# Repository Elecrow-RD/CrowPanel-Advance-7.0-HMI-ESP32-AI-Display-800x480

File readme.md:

## Menu
### 1, Product picture
### 2, Product version number
### 3, product information
### 4, Use the driver module
### 5,Quick Start
### 6,Folder structure.
### 7,Pin definition
### 8,Guidelines for downloading some of the files from the github repository

### 1, Product picture

#### 2, Product version number

|      | Hardware | Software | Remark |
| ---- | -------- | -------- | ------ |
| 1    | V1.0     | V1.0     | old    |
| 2    | V1.2     | V1.2     | latest |

### 3, product information

| Main Chip-ESP32-S3-WROOM-1-N16R8         |                                                              |
| -------------------------------------------- | ------------------------------------------------------------ |
| CPU/SoC                                      | high-performance Xtensa 32-bit LX7 dual-core processor, with up to 240MHz |
| System Memory                                | 512KB SRAM、8M PSRAM                                         |
| Memory                                       | 16M Flash，384KB ROM                                         |
| Development Language                         | MicroPython、C/C++                                           |
| Development Environment                      | ESP-IDF、Arduino IDE、PlatformIO、Micro Python、LVGL         |
| **Screen**                                   |                                                              |
| Size                                         | 7.0 inch                                                     |
| Diver IC                                     | SC7277                                                       |
| Resolution                                   | 800*480                                                      |
| Display Panel                                | IPS Panel                                                    |
| Touch Panel                                  | Capacitive Single Touch                                      |
| Viewing Angle                                | 178°                                                         |
| Brightness                                   | 400 cd/m²(Typ.)                                              |
| Color Depth                                  | 16-bit                                                       |
| **Wireless Communication - Onboard Antenna** |                                                              |
| WiFi                                         | Support 2.4GHz, 802.11a/b/g/n                                |
| Bluetooth                                    | Support Bluetooth 5.0 and BLE                                |
| Other                                        | **Zigbee、LoRa、nRF2401、Matter、Thread and Wi-Fi 6 (Optional)** |
| **Interface/Function**                       |                                                              |
| Interface                                    | USB port, UART, I2C, SD card slot, battery socket, speaker port, microphone, etc. |
| Function                                     | RTC clock, audio amplifier, volume control, battery charge management, USB to UART, etc. |
| **Button/LED Indicator**                     |                                                              |
| Reset Button                                 | Yes, press to reset the device                               |
| Boot Button                                  | Yes, press and hold the power button to burn the program     |
| PWR                                          | Power indicator                                              |
| CHG                                          | Lithium battery charging status, completion indication       |
| **Other**                                    |                                                              |
| Installation method                          | Back hanging, fixed hole                                     |
| Operating temperature                        | -20~70 °C                                                    |
| Storage temperature                          | -30~80 °C                                                    |
| Power Input                                  | 5V/2A, USB or UART terminal                                  |
| Active Area                                  | 156mm*87mm                                                   |
| Dimensions                                   | 181.26*108.36*16mm                                           |

### 4, Use the driver module

| Name | dependency library                      |
| ---- | --------------------------------------- |
| LVGL | lvgl/lvgl@8.3.3                         |
|      | Adafruit GFX Library<br/>version=1.11.0 |

### 5,Quick Start
### Arduino IDE starts

#### Teaching Case Path：./example/example_code7.0

1.Download the library files used by this product to the 'libraries' folder.

C:\Users\Documents\Arduino\libraries\

2.Open the Arduino IDE

3.Open the code configuration environment and burn it

### ESP-IDF starts

#### Teaching Case Path：./example/idf_code

1.Right-click on an empty space in the project folder and select "Open with VS Code" to open the project.

2.In the IDF plug-in, select the port, then compile and flash

### 6,Folder structure.

|--3D file： Contains 3D model files (.stp) for the hardware. These files can be used for visualization, enclosure design, or integration into CAD software.

|--Datasheet: Includes datasheets for components used in the project, providing detailed specifications, electrical characteristics, and pin configurations.

|--Eagle_SCH&PCB: Contains **Eagle CAD** schematic (`.sch`) and PCB layout (`.brd`) files. These are used for circuit design and PCB manufacturing.

|--example: Provides example code and projects to demonstrate how to use the hardware and libraries. These examples help users get started quickly.

|--factory_firmware: Stores pre-compiled factory firmware that can be directly flashed onto the device. This ensures the device runs the default functionality.

|--factory_sourcecode:  Contains the source code for the factory firmware, allowing users to modify and rebuild the firmware as needed.

|--libraries: Includes necessary libraries required for compiling and running the project. These libraries provide drivers and additional functionalities for the hardware.

|--Squareline_studio Instructions for use: Squareline_studio instructions: Demonstrate the use of squareline studio.

### 7,Pin definition

#define HSPI_MISO  4
#define HSPI_MOSI  6
#define HSPI_SCLK  5
#define HSPI_SS    19

#define SD_MOSI 6
#define SD_MISO 4
#define SD_SCK  5
#define SD_CS   7 //The chip selector pin is not connected to IO

#define I2S_DOUT 12
#define I2S_BCLK 13
#define I2S_LRC 11

cfg.pin_sclk = 42;  // SPI、SCLK

cfg.pin_mosi = 39;  // SPI、CLK

cfg.pin_miso = -1;  // SPI、MISO

cfg.pin_dc = 41; 

#define TOUCH_GT911_SCL 16
#define TOUCH_GT911_SDA 15

### 8,Guidelines for downloading some of the files from the github repository

##### 1, open the link in your browser: https://downgit.github.io/

##### 2, paste the URL of the GitHub destination folder in the input box (example format: `https://github.com/username/repository name/tree/branch name/folder path`)

##### 3, even a that way to download the file.

①Click the “Create Download Link” button to create a download link, copy the link and open it with your browser to download the contents of the corresponding folder directly.

②Click Download, and you can also download it directly.

#### Note: DownGit downloads are stored by default in **your browser's default downloads folder**, usually:

- **Windows**: `C:\Users\your username\Downloads\` (downloads folder)
- **macOS**: `~/Downloads/` (downloads folder)
- **Linux**: `~/Downloads/` (Downloads folder)

If you change the default download path in your browser, the file will be stored in the download location you set. You can find the downloaded file path in your browser's **Download History** (shortcut `Ctrl + J` or `Cmd + J`).

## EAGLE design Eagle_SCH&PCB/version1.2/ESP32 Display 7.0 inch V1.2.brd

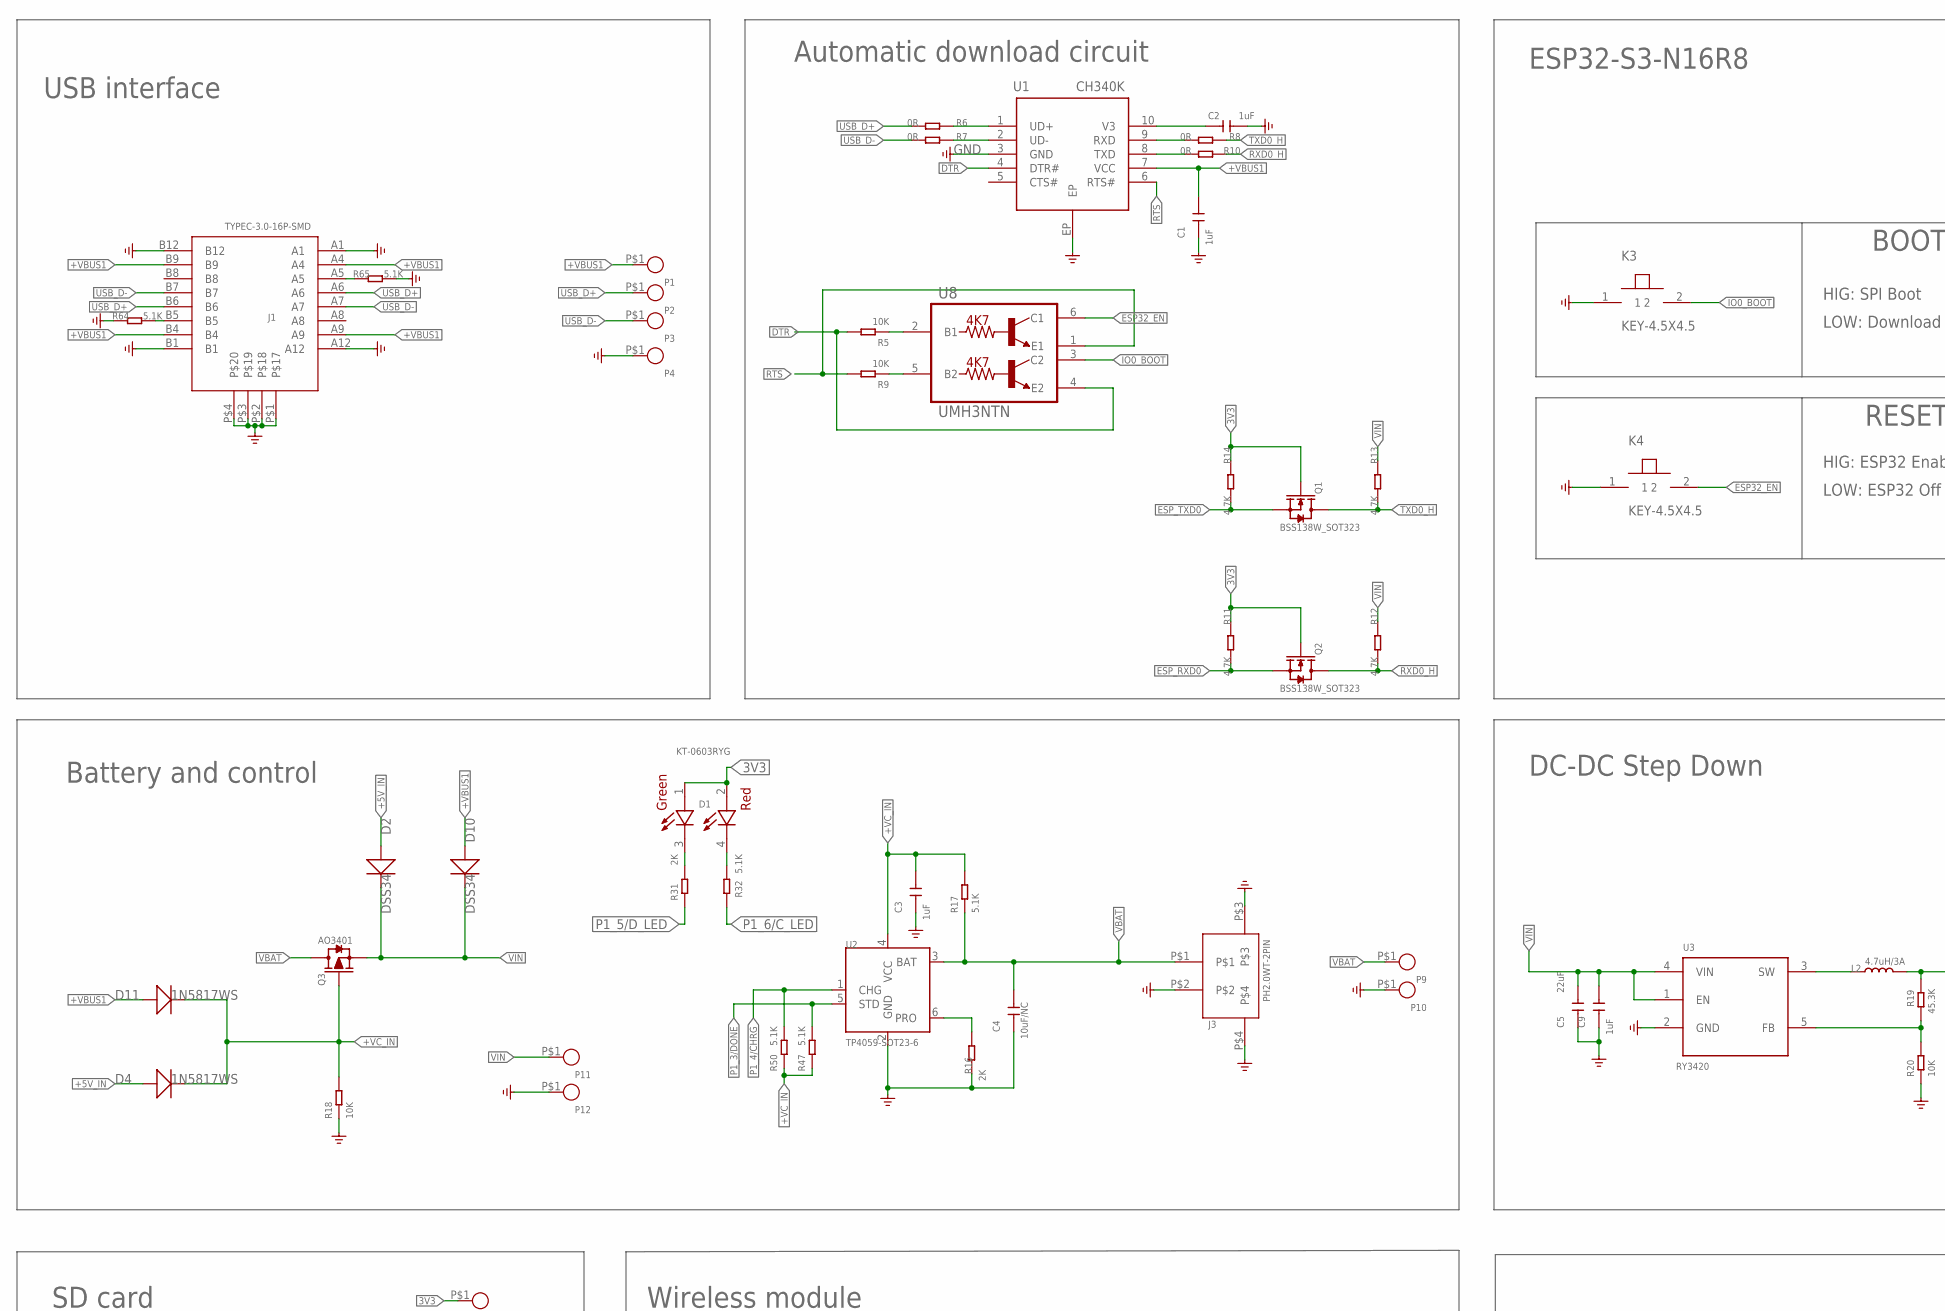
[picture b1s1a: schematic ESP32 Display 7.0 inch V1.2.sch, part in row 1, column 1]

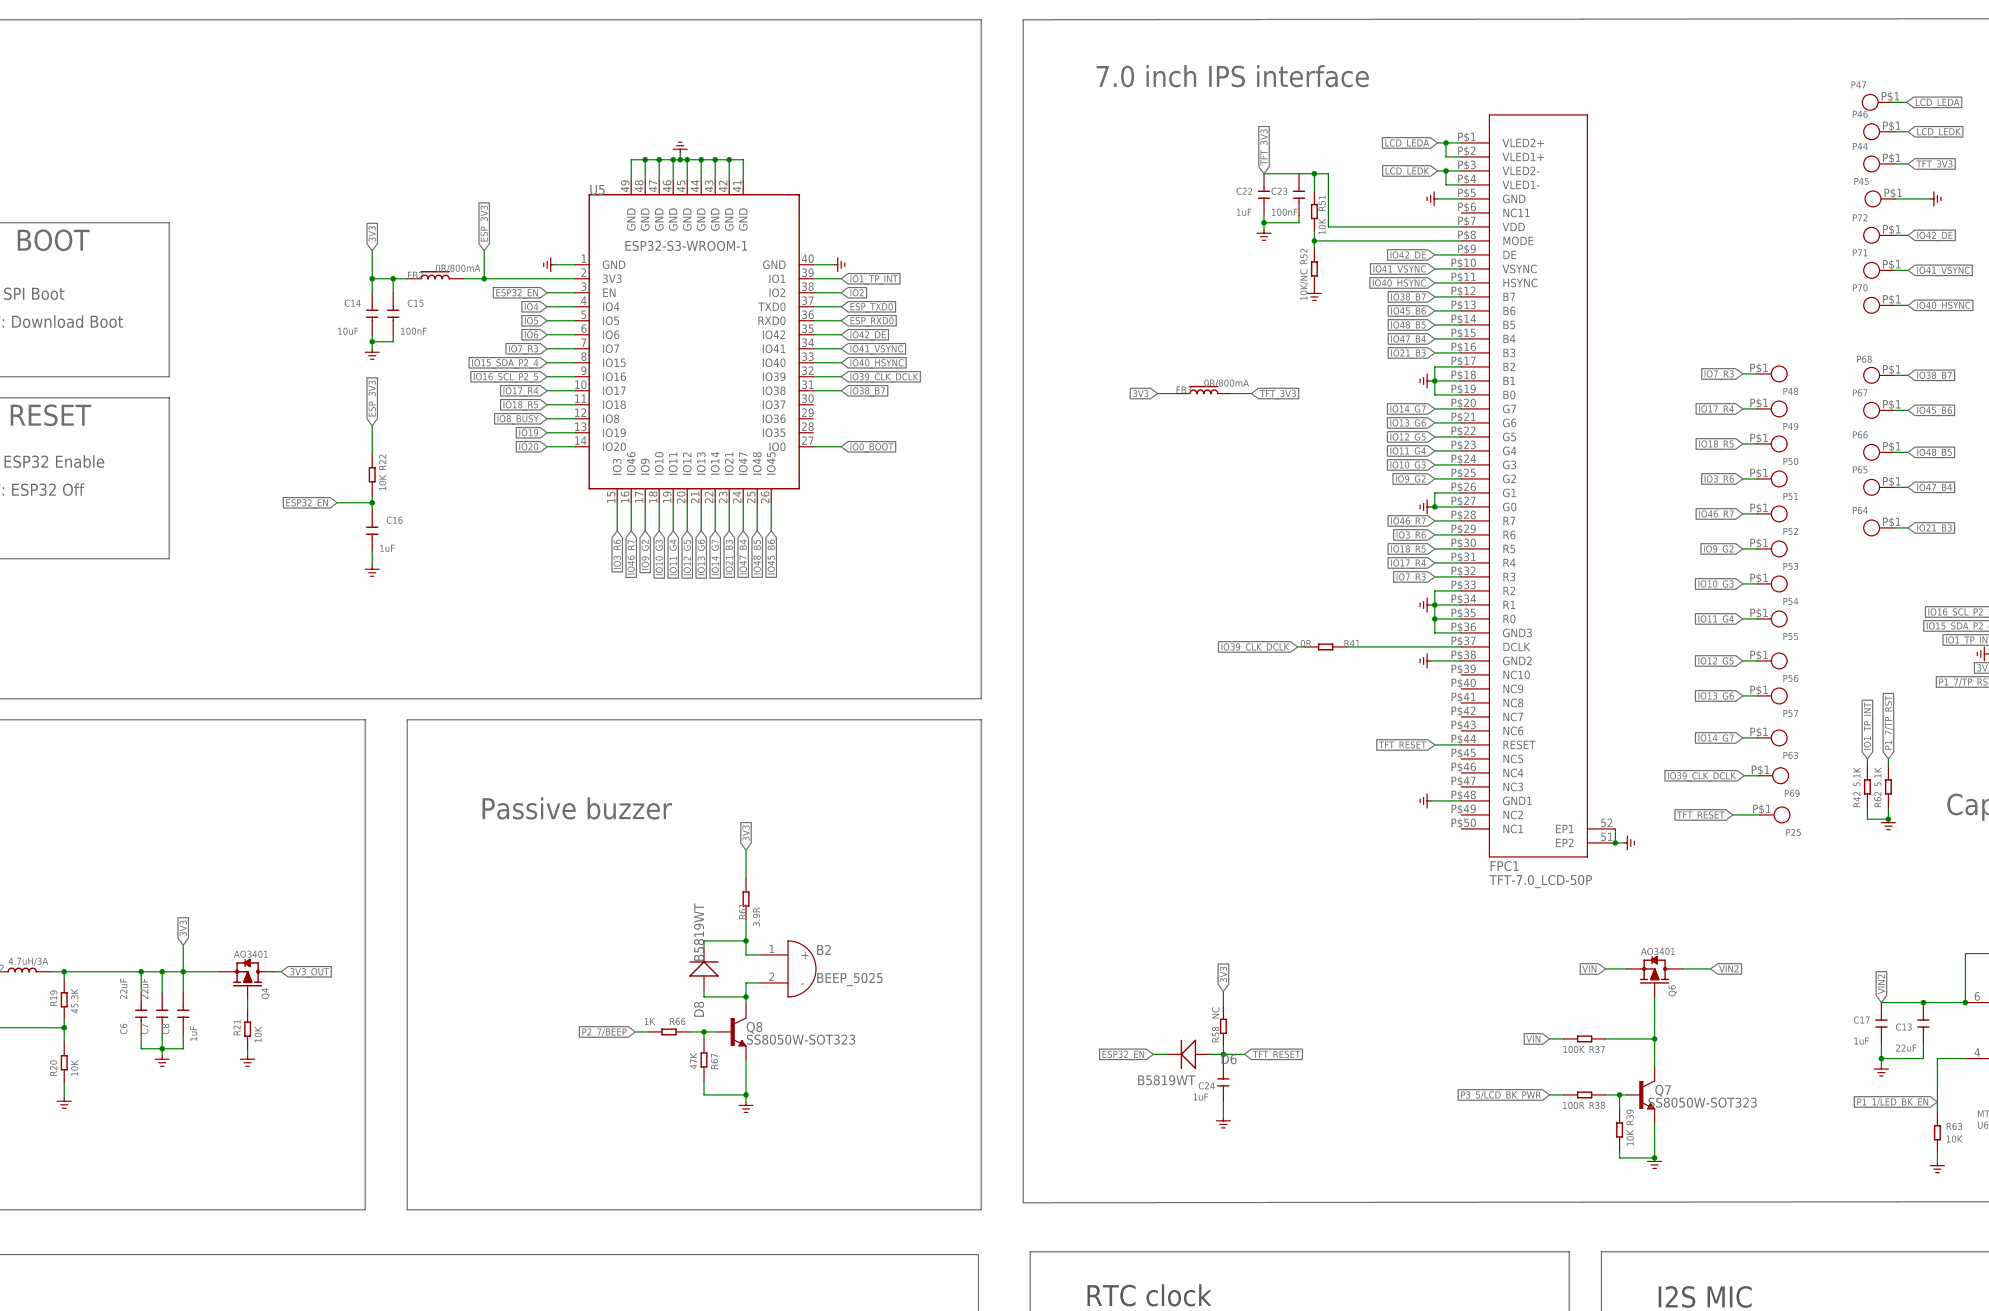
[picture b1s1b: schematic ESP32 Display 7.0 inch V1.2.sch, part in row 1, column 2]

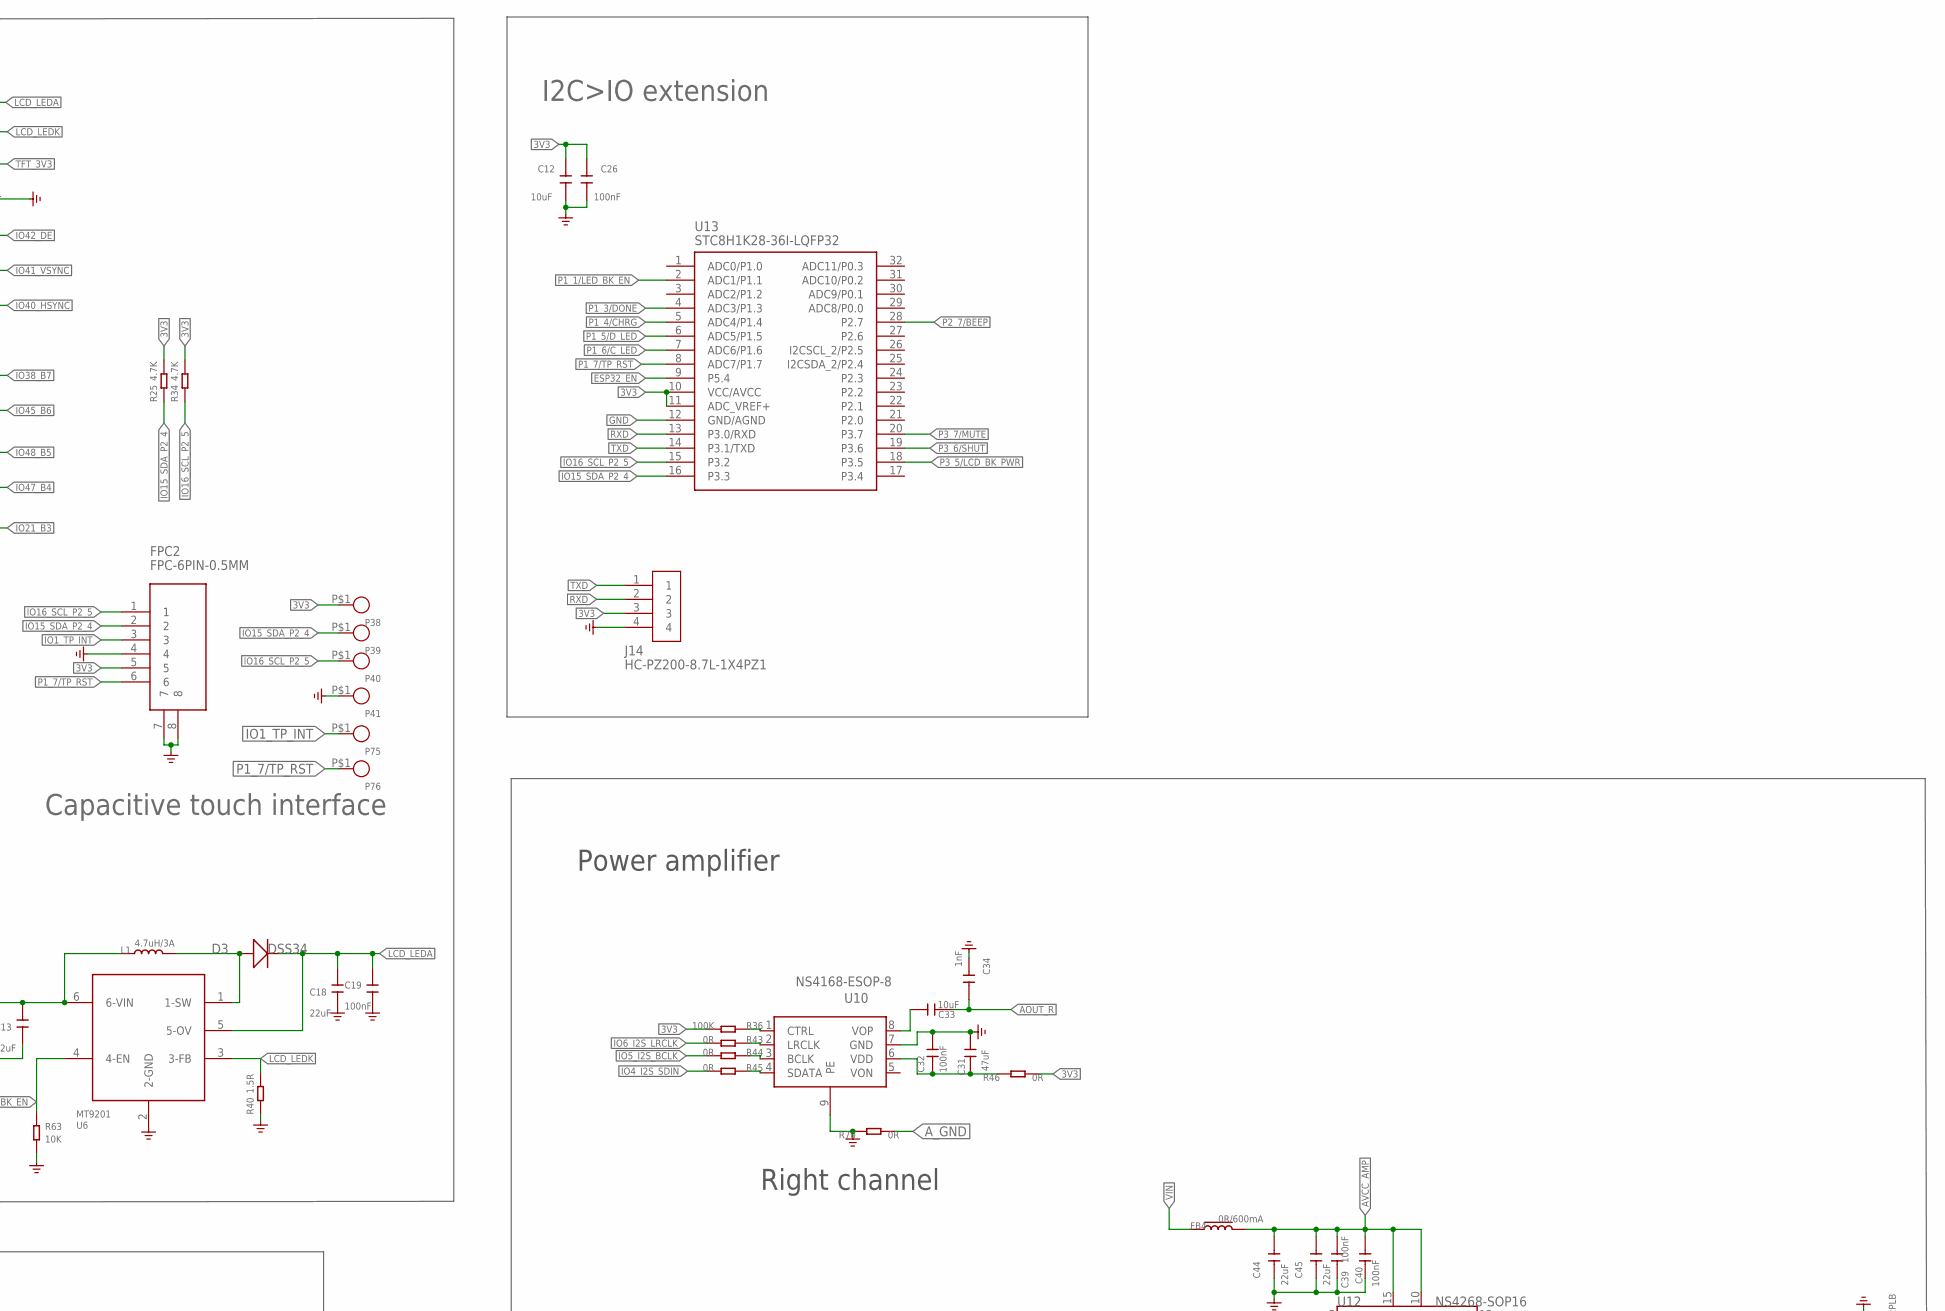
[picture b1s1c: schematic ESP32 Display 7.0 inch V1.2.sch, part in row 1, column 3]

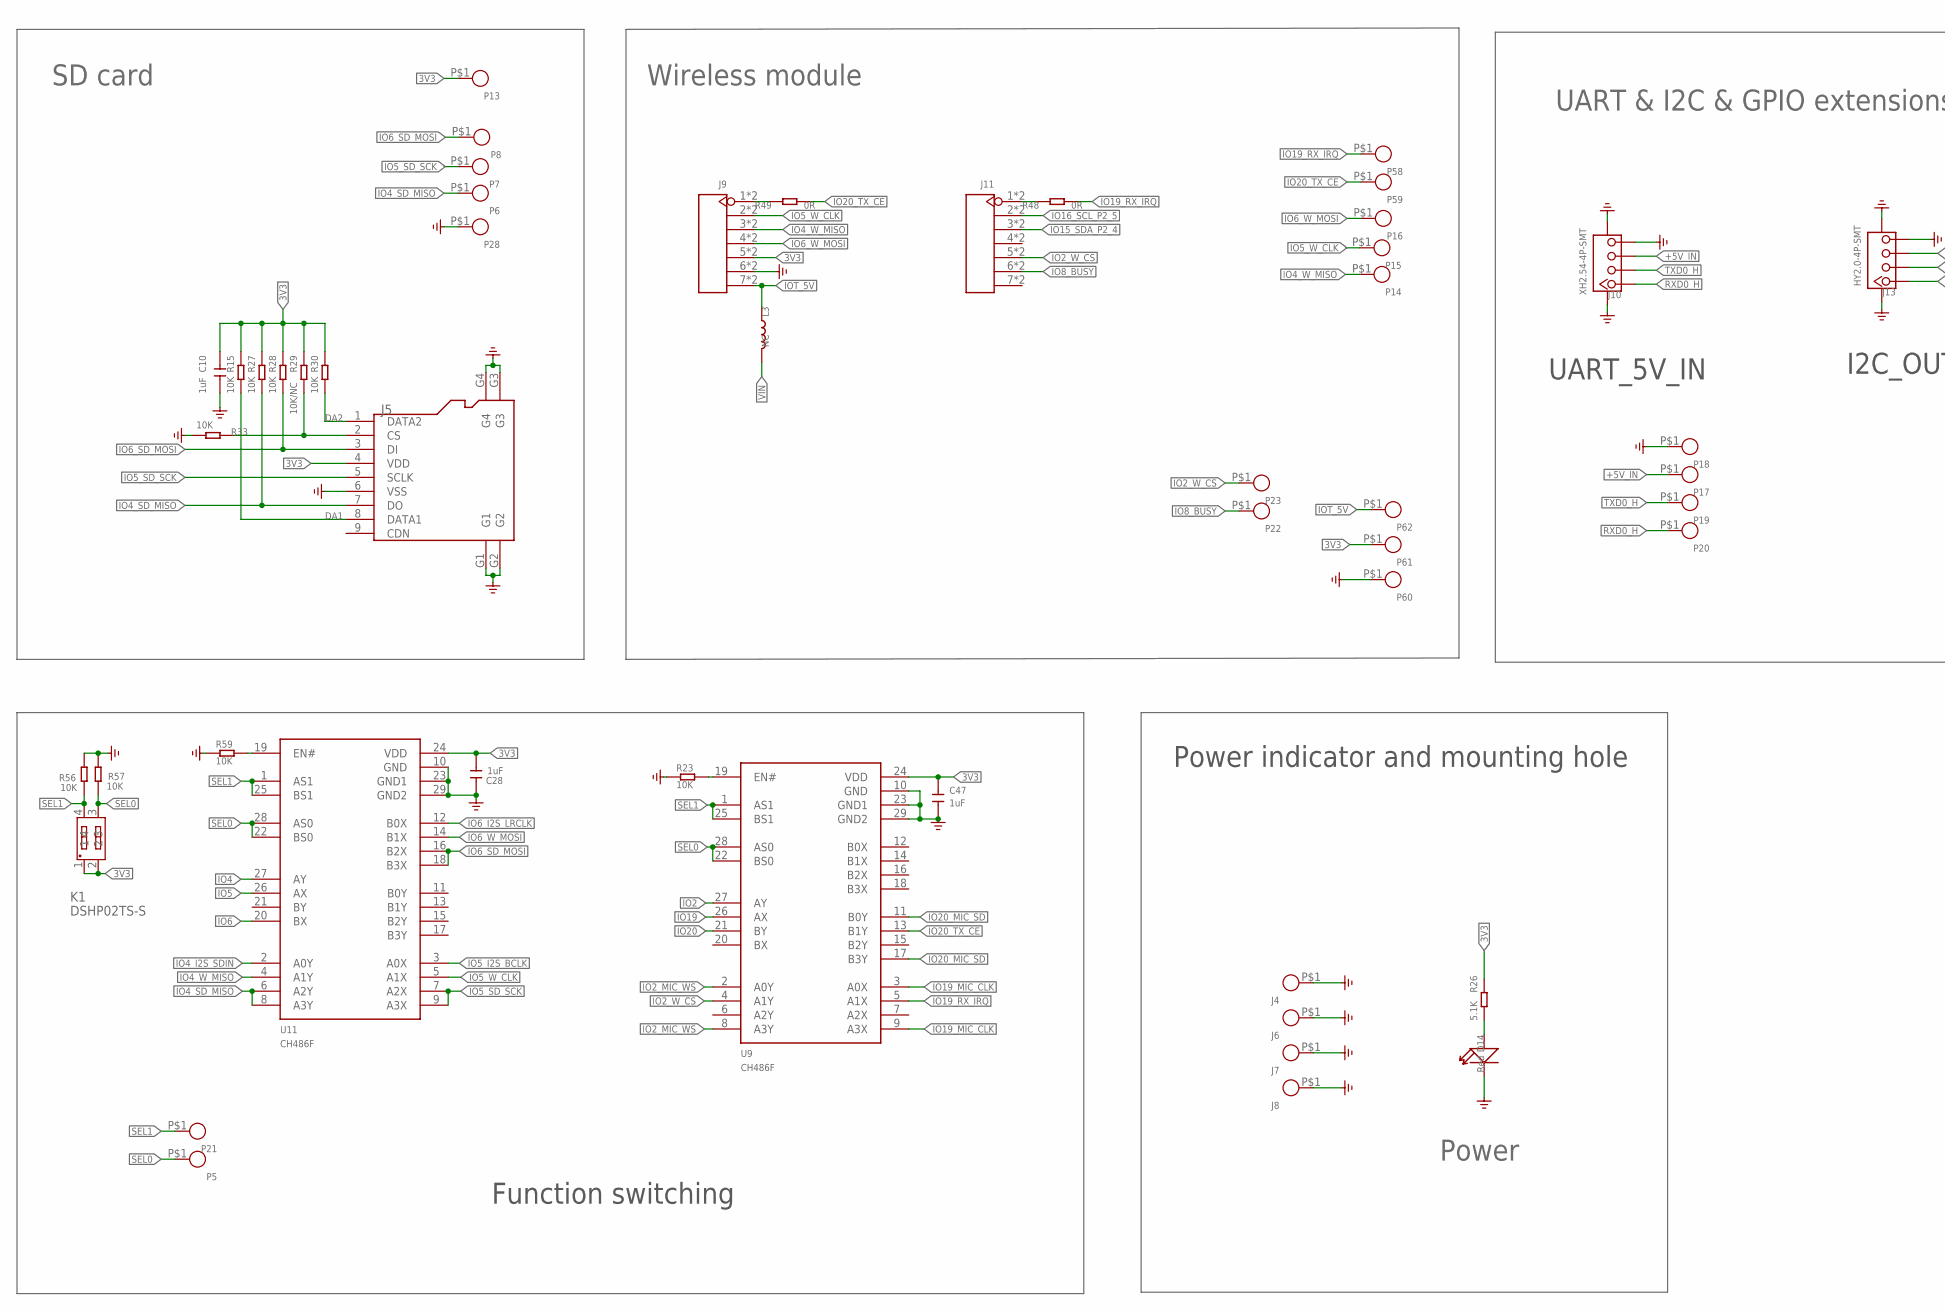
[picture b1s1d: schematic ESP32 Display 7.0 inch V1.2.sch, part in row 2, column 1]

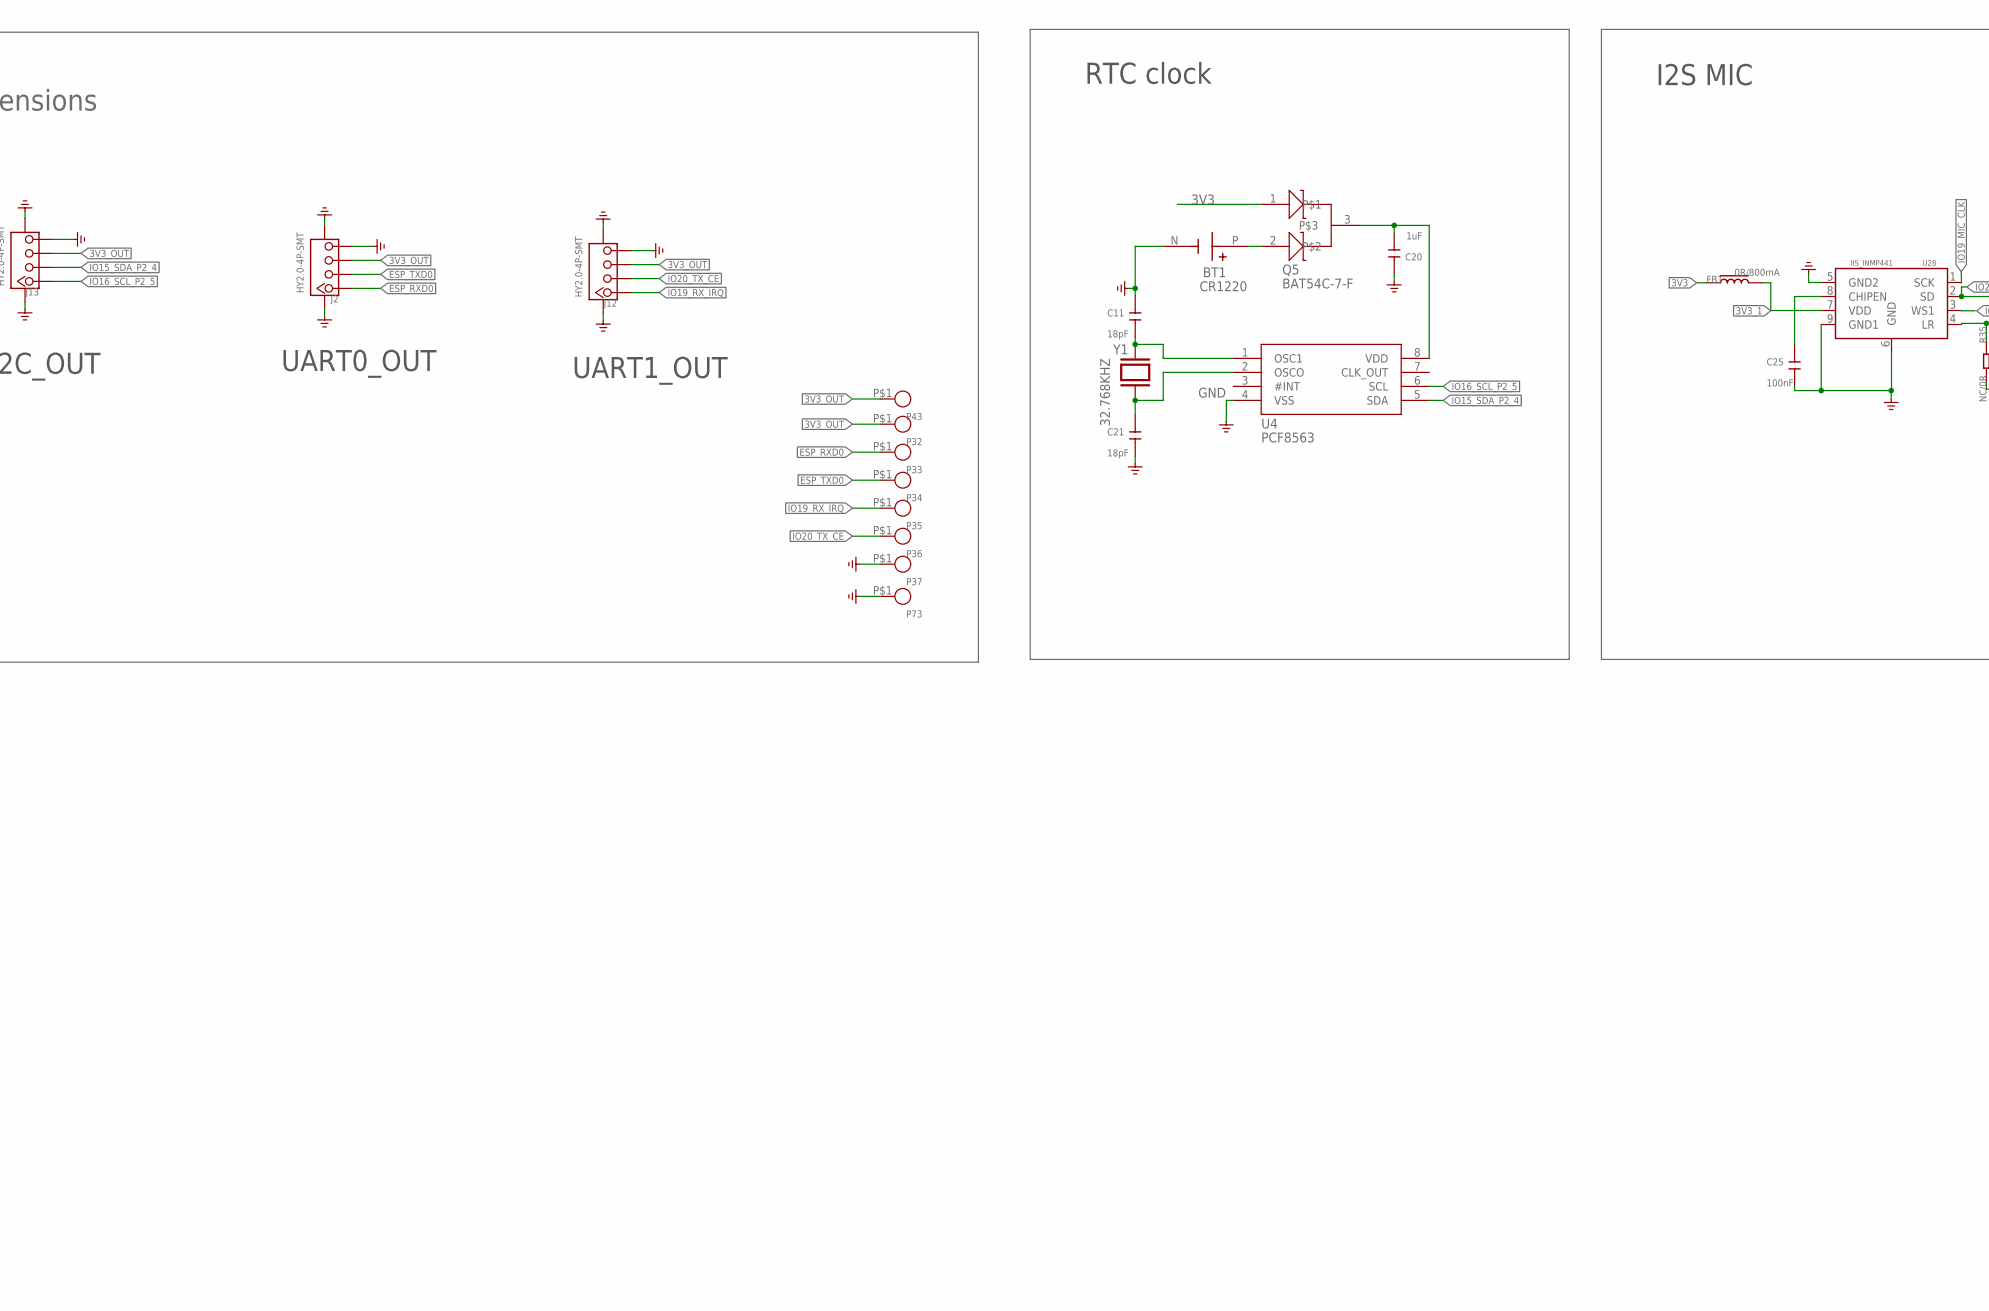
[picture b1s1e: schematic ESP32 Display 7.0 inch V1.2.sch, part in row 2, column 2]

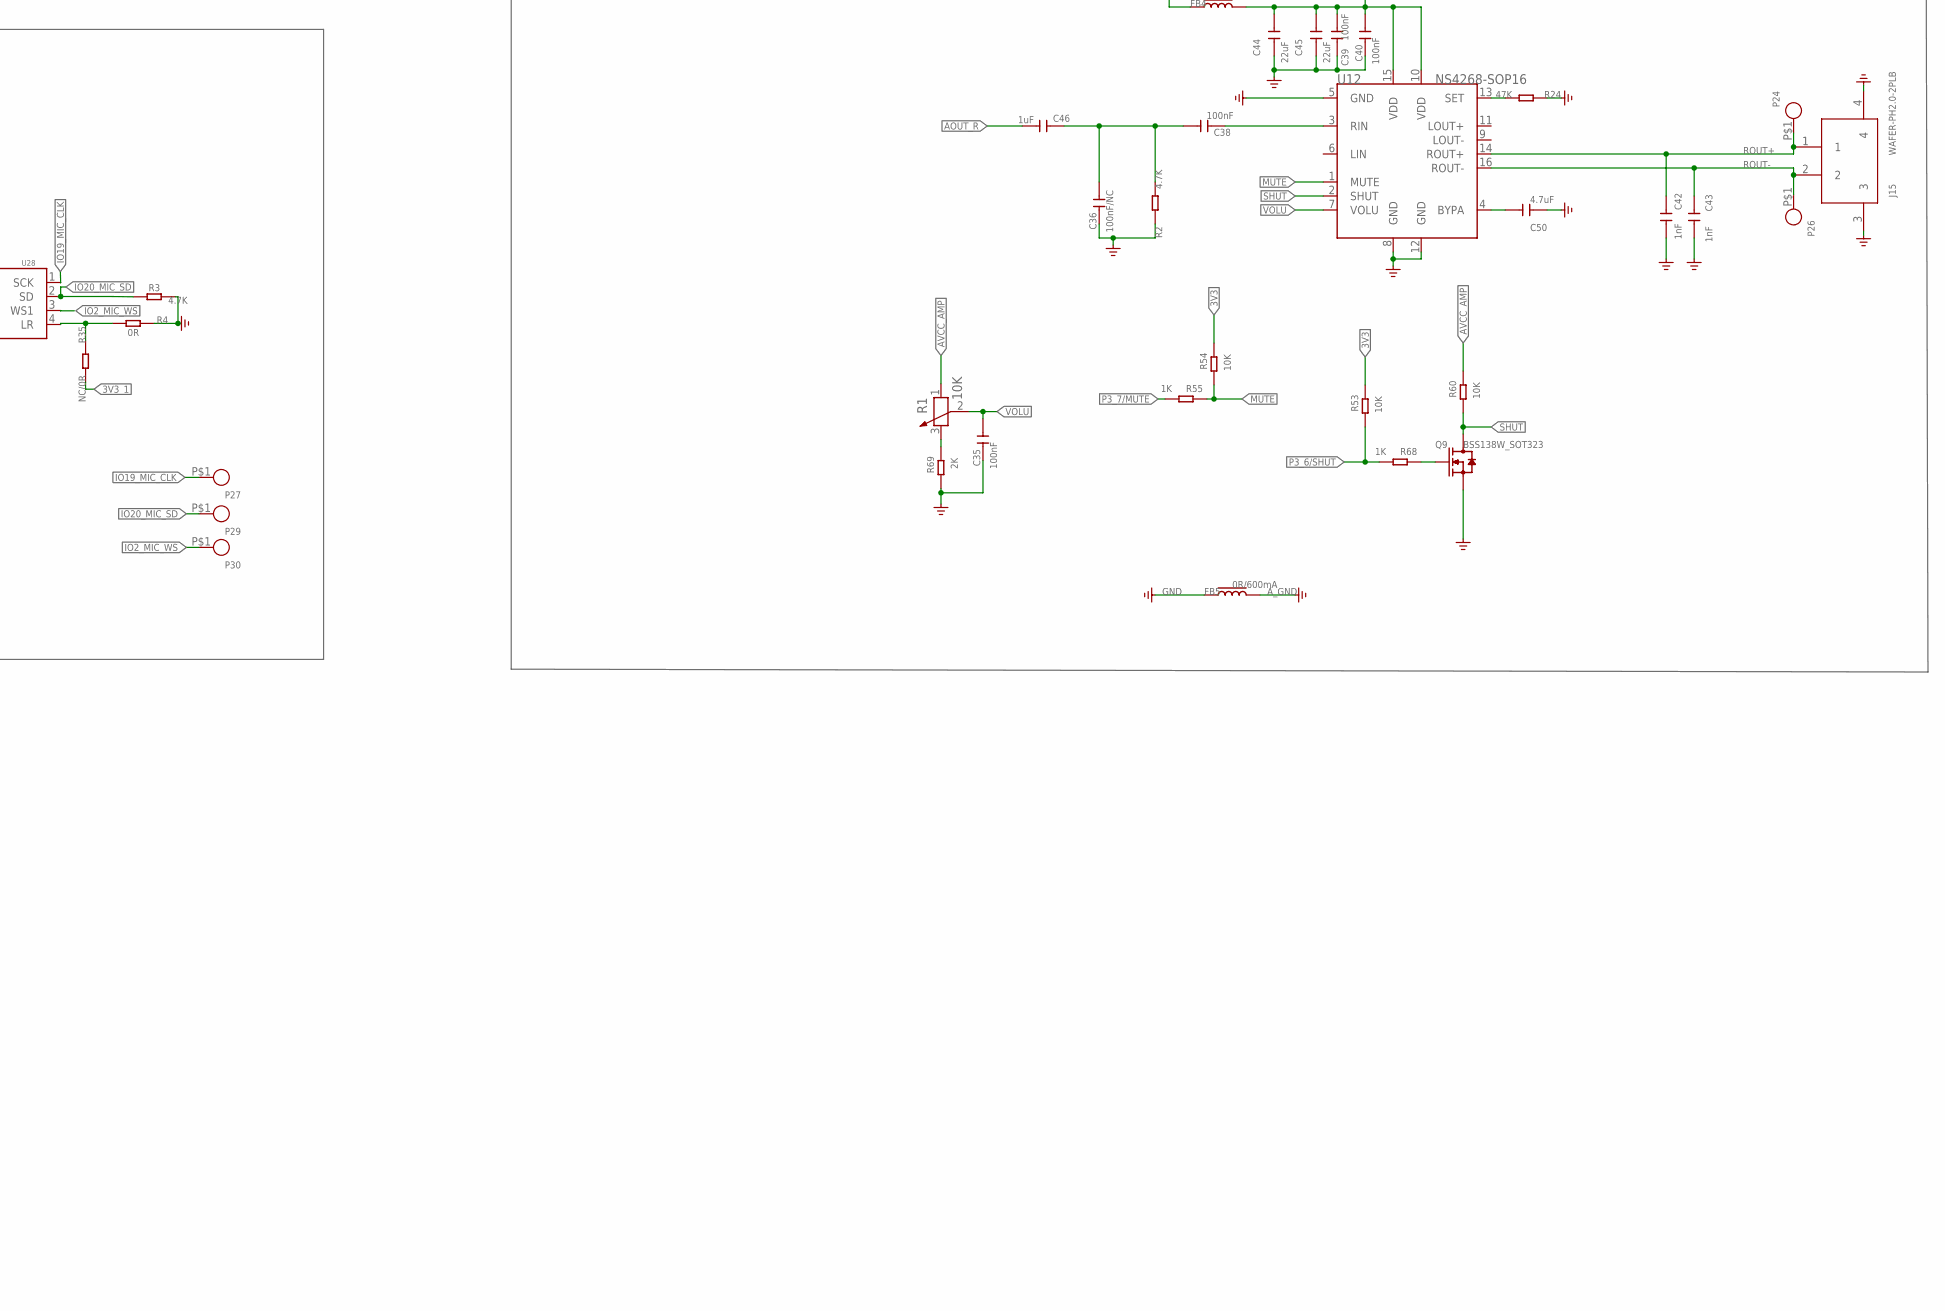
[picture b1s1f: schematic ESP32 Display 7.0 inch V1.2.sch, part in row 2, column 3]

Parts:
B2: BEEP_5025
BT1: CR1220
C1, C2, C3, C8, C9, C10, C16, C17, C20, C22, C24, C28, C46, C47: 1uF; C0603
C4: 10uF/NC; C0603
C5, C6, C7, C13, C18, C44, C45: 22uF; C0805
C11, C21: 18pF; C0603
C12, C14, C33: 10uF; C0603
C15, C19, C23, C25, C26, C32, C35, C38, C39, C40: 100nF; C0603
C31: 47uF; C0805
C34, C42, C43: 1nF; C0603
C36: 100nF/NC; C0603
C50: 4.7uF; C0603
D1: KT-0603RYG; LED_KT-0603RYG
D2, D3, D10: DSS34; D_SOD123FL
D4, D11: 1N5817WS; D_SOD323
D6, D8: B5819WT; D_SOD523
D14: Red; LED0603
FB1, FB2, FB3: 0R/800mA; L0603
FB4, FB5: 0R/600mA; L0603
FPC1: TFT-7.0_LCD-50P; FPC-P0.5MM-50P-SMD
FPC2: FPC-6PIN-0.5MM
J1: TYPEC-3.0-16P-SMD; USB-3.0TYPEC-SMD
J2, J12, J13: HY2.0-4P-SMT; CONNECTOR_4P-SMD-2.0
J3: PH2.0WT-2PIN
J4, J6, J7, J8: THO-M3.25MM-HOLE; THO-M3.2*5MM-HOLE
J5: HOLDER-MICROSD-9P; 9P-SMD-W/-RING
J9, J11: HEADER-7P-18.28X2.5; H7-2.54-18.28X2.5X5MM
J10: XH2.54-4P-SMT; XH2.54-4P-SMD
J14: HC-PZ200-8.7L-1X4PZ1; TEST-PIN-4-2.0MM
J15: WAFER-PH2.0-2PLB; CONN-TH_2P-P2.00_XUNPU_WAFER-PH2.0-2PLB
K1: DSHP02TS-S; SW-SMD_DSHP02TS-S_1
K3, K4: KEY-4.5X4.5; KEY-4.5X4.5-SMD
L1, L2: 4.7uH/3A; L0420
L3: NC; L0603
P1, P2, P3, P4, P5, P6, P7, P8, P9, P10, P11, P12, P13, P14, P15, P16, P17, P18, P19, P20, P21, P22, P23, P24, P25, P26, P27, P28, P29, P30, P32, P33, P34, P35, P36, P37, P38, P39, P40, P41, P43, P44, P45, P46, P47, P48, P49, P50, P51, P52, P53, P54, P55, P56, P57, P58, P59, P60, P61, P62, P63, P64, P65, P66, P67, P68, P69, P70, P71, P72, P73, P75, P76: TEST_PADPAD-1.5MM; TEST_PAD-1.5MM
Q1, Q2, Q9: BSS138W_SOT323; MOS_SOT323
Q3, Q4, Q6: AO3401; PMOS_SOT23
Q5: BAT54C-7-F; SOT-23
Q7, Q8: SS8050W-SOT323; MOS_SOT323
R1: 10K; 3P-SMD-SQUA-3.6X3.3
R2, R3, R11, R12, R13, R14, R25, R34: 4.7K; R0603-SP
R4, R6, R7, R8, R10, R41, R43, R44, R45, R46, R48, R49, R70: 0R; R0603-SP
R5, R9, R15, R18, R20, R21, R22, R23, R27, R28, R30, R33, R39, R51, R53, R54, R56, R57, R59, R60, R63: 10K; R0603-SP
R16, R31, R69: 2K; R0603-SP
R17, R26, R32, R42, R47, R50, R62, R64, R65: 5.1K; R0603-SP
R19: 45.3K; R0603-SP
R24, R67: 47K; R0603-SP
R29, R52: 10K/NC; R0603-SP
R35: NC/0R; R0603-SP
R36, R37: 100K; R0603-SP
R38: 100R; R0603-SP
R40: 1.5R; R0603-SP
R55, R66, R68: 1K; R0603-SP
R58: NC; R0603-SP
R61: 3.9R; R0603-SP
U1: CH340K; ESOP-10-EP-150MIL
U2: TP4059-SOT23-6; SOT23-6L
U3: RY3420; IC_SOT23-5
U4: PCF8563; MSOP-8
U5: ESP32-S3-WROOM-1; ESP32-S3-WROOM-1-SMD41
U6: MT9201; COOPER_SOT23-6
U8: UMH3NTN; SOP65P210X100-6N
U9, U11: CH486F; QFN-28_L4.0-W4.0-P0.40-BL-EP2.8
U10: NS4168-ESOP-8
U12: NS4268-SOP16; SOP-16
U13: STC8H1K28-36I-LQFP32; QFP80P900X900X165-32N
U28: IIS_INMP441
Y1: 32.768KHZ; SMD3215-2P

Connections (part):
3V3: C6.2, C7.2, C8.2, C10.2, C12.2, C14.2, C15.2, C26.2, C28.2, C47.1, D1.1, D1.2, FB1.1, FB2.1, FB3.1, FPC2.5, J5.4 (VDD), J9.5, J9.5-5 (5), J14.3, K1.1, K1.2, L2.2, P13.P$1, P38.P$1, P61.P$1, Q1.1 (G), Q2.1 (G), Q4.2 (S), Q5.1, R11.1, R14.1, R15.2, R19.2, R25.2, R26.2, R27.2, R28.2, R29.2, R30.2, R34.2, R36.2, R46.2, R53.1, R54.1, R58.2, R61.2, U9.24 (VDD), U11.24 (VDD), U13.10 (VCC/AVCC), U13.11 (ADC_VREF+)
3V3$: C2.2, U1.10 (V3)
3V3_1: C25.2, FB1.2, R35.2, U28.7 (VDD), U28.8 (CHIPEN)
3V3_OUT: J2.3, J12.3, J13.3, P32.P$1, P43.P$1, Q4.3 (D)
+5V_IN: D2.+, D4.+, J10.3, P17.P$1
+VBUS1: C1.2, D10.+, D11.+, J1.A4, J1.A9, J1.B4, J1.B9, P1.P$1, U1.7 (VCC)
+VC_IN: C3.2, D4.-, D11.-, Q3.1 (G), R17.2, R18.2, R47.2, R50.2, U2.4 (VCC)
AOUT_R: C33.1, C34.2, C46.2
AVCC_AMP: C39.2, C40.2, C44.2, C45.2, FB4.2, R1.1, R60.1, U12.10 (VDD), U12.15 (VDD)
A_GND: C35.1, C36.1, C39.1, C40.1, C42.1, C43.1, C44.1, C45.1, C50.1, FB5.2, J15.3, J15.4, Q9.2 (S), R2.1, R24.1, R69.2, R70.2, U12.5 (GND), U12.8 (GND), U12.12 (GND)
DA1: J5.8 (DATA1), R15.1
DA2: J5.1 (DATA2), R30.1
DTR: R5.2, U1.4 (DTR#), U8.4 (E2)
ESP32_EN: C16.2, D6.-, K4.2, R22.2, U5.3 (EN), U8.6 (C1), U13.9 (P5.4)
ESP_3V3: FB2.2, R22.1, U5.2 (3V3)
ESP_RXD0: J2.1, P33.P$1, Q2.2 (S), R11.2, U5.36 (RXD0)
ESP_TXD0: J2.2, P34.P$1, Q1.2 (S), R14.2, U5.37 (TXD0)
GND: BT1.N (-), C1.1, C2.1, C3.1, C4.1, C5.1, C6.1, C7.1, C8.1, C9.1, C10.1, C11.2, C12.1, C13.2, C14.1, C15.1, C16.1, C17.1, C18.2, C19.1, C20.2, C21.1, C22.1, C23.1, C24.1, C25.1, C26.1, C28.1, C31.2, C32.2, C34.1, C47.2, D14.-, FB5.1, FPC1.51 (EP2), FPC1.52 (EP1), FPC1.P$5 (GND), FPC1.P$17 (B2), FPC1.P$18 (B1), FPC1.P$19 (B0), FPC1.P$26 (G1), FPC1.P$27 (G0), FPC1.P$33 (R2), FPC1.P$34 (R1), FPC1.P$35 (R0), FPC1.P$36 (GND3), FPC1.P$38 (GND2), FPC1.P$48 (GND1), FPC2.4, FPC2.7, FPC2.8, J1.A1, J1.A12, J1.B1, J1.B12, J1.P$1, J1.P$2, J1.P$3, J1.P$4, J2.4, J2.SS1, J2.SS2, J3.P$2, J3.P$3, J3.P$4, J4.P$1, J5.6 (VSS), J5.G1, J5.G2, J5.G3, J5.G4, J6.P$1, J7.P$1, J8.P$1, J9.6, J9.6-6 (6), J10.4, J10.5 (SS1), J10.6 (SS2), J12.4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
IO0_BOOT: K3.2, U5.27 (IO0), U8.3 (C2)
IO1_TP_INT: FPC2.3, P75.P$1, R42.2, U5.39 (IO1)
IO2: U5.38 (IO2), U9.27 (AY)
IO2_MIC_WS: P30.P$1, U9.2 (A0Y), U9.8 (A3Y), U28.3 (WS1)
IO2_W_CS: J11.5, J11.5-5 (5), P23.P$1, U9.4 (A1Y)
IO3_R6: FPC1.P$29 (R6), P51.P$1, U5.15 (IO3)
IO4: U5.4 (IO4), U11.27 (AY)
IO4_I2S_SDIN: R45.2, U11.2 (A0Y)
IO4_SD_MISO: J5.7 (DO), P6.P$1, R27.1, U11.6 (A2Y), U11.8 (A3Y)
IO4_W_MISO: J9.3, J9.3-3 (3), P14.P$1, U11.4 (A1Y)
IO5: U5.5 (IO5), U11.26 (AX)
IO5_I2S_BCLK: R44.2, U11.3 (A0X)
IO5_SD_SCK: J5.5 (SCLK), P7.P$1, U11.7 (A2X), U11.9 (A3X)
IO5_W_CLK: J9.2, J9.2-2 (2), P15.P$1, U11.5 (A1X)
IO6: U5.6 (IO6), U11.20 (BX)
IO6_I2S_LRCLK: R43.2, U11.12 (B0X)
IO6_SD_MOSI: J5.3 (DI), P8.P$1, R28.1, U11.16 (B2X), U11.18 (B3X)
IO6_W_MOSI: J9.4, J9.4-4 (4), P16.P$1, U11.14 (B1X)
IO7_R3: FPC1.P$32 (R3), P48.P$1, U5.7 (IO7)
IO8_BUSY: J11.6, J11.6-6 (6), P22.P$1, U5.12 (IO8)
IO9_G2: FPC1.P$25 (G2), P53.P$1, U5.17 (IO9)
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
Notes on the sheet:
BOOT
RESET
HIG: SPI Boot
LOW: Download Boot
HIG: ESP32 Enable
LOW: ESP32 Off
Power
USB interface
Automatic download circuit
Battery and control
RTC clock
ESP32-S3-N16R8
7.0 inch IPS interface
Capacitive touch interface
DC-DC Step Down
SD card
Wireless module
UART & I2C & GPIO extensions
Power indicator and mounting hole
I2C>IO extension
I2S MIC
Power amplifier
Right channel
Passive buzzer
Function switching
UART_5V_IN
I2C_OUT
UART0_OUT
UART1_OUT

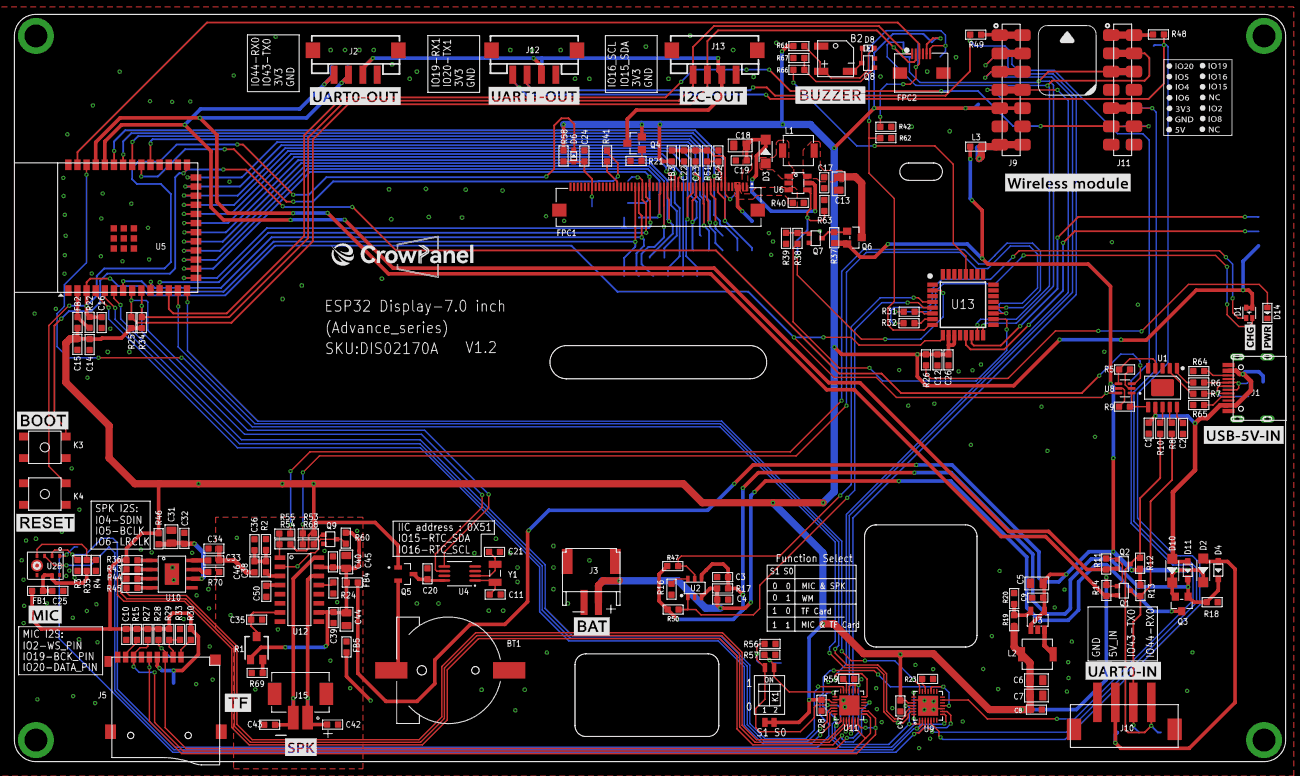
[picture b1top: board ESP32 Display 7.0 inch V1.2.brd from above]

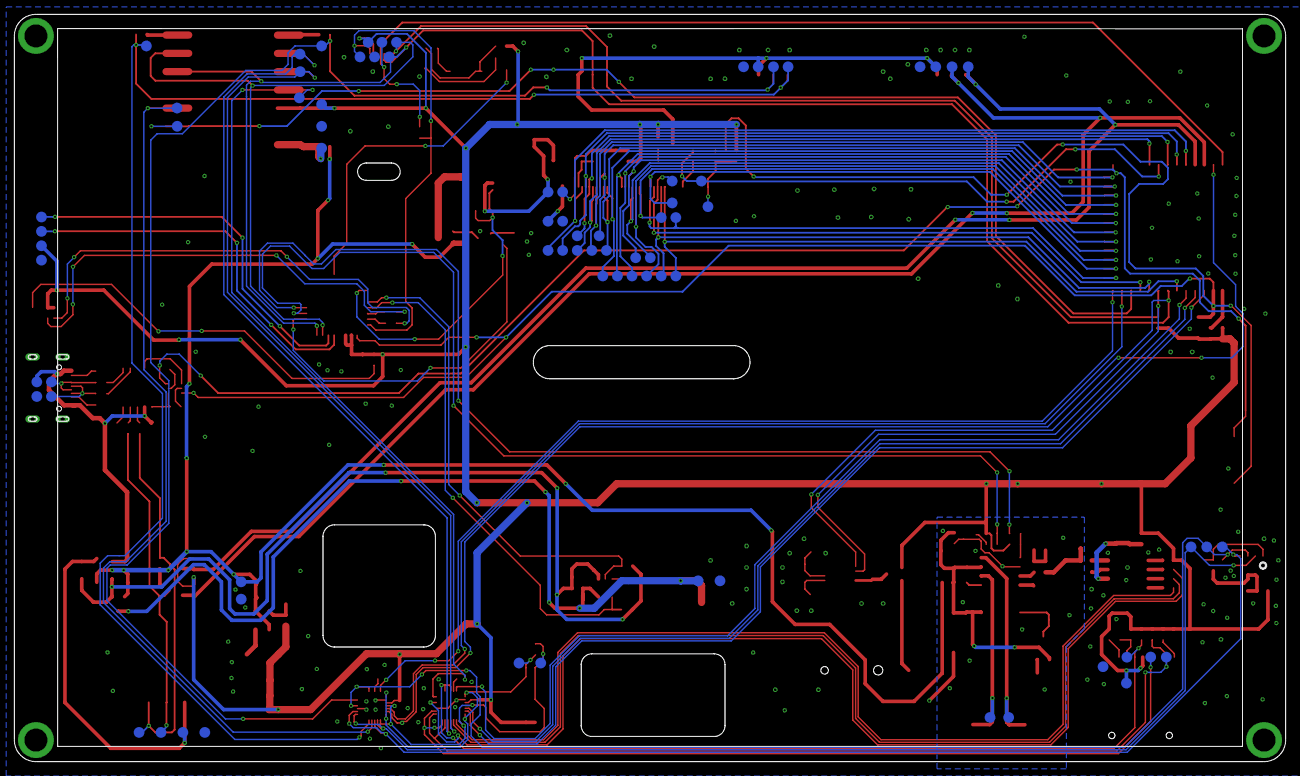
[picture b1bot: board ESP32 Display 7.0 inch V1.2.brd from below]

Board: 2 copper layers, 176.9 x 104.0 mm, 248 parts (74 on the bottom side), 141 nets.
